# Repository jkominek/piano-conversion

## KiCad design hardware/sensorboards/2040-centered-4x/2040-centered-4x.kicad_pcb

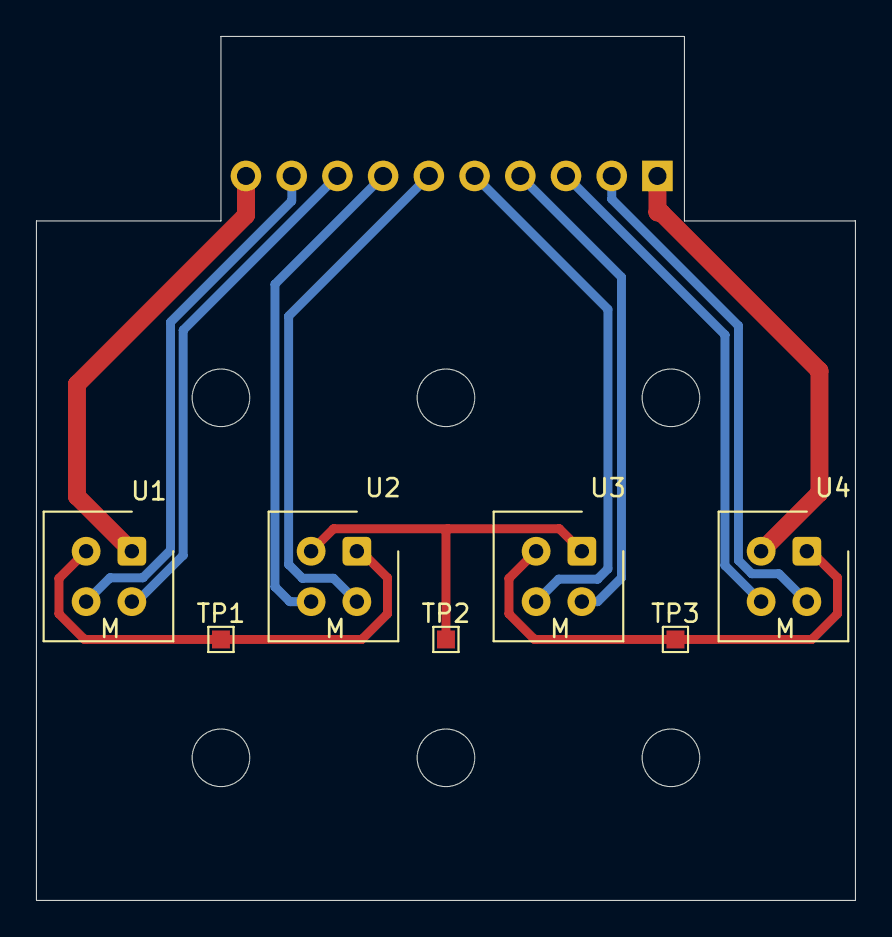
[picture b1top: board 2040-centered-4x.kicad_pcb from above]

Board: 2 copper layers, 45.5 x 48.0 mm, 14 parts (1 on the bottom side), 13 nets.

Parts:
H1, H2, H3, H4, H5, H6: MountingHole; MountingHole_3.2mm_M3
J1: Conn_01x10_Male; Pin_Header_Angled_1x10_Pitch2.54mm
TP1, TP2, TP3: TestPoint; TestPoint_Pad_1.0x1.0mm
U1, U2, U3, U4: CNY70; Vishay_CNY70

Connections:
/C1: J1.9, U1.3
/C2: J1.7, U2.3
/C3: J1.5, U3.3
/C4: J1.3, U4.3
/E1: J1.8, U1.4
/E2: J1.6, U2.4
/E3: J1.4, U3.4
/E4: J1.2, U4.4
/NEG: J1.1, U4.2
/POS: J1.10, U1.1
unnamed: TP1.1, U1.2, U2.1
unnamed: TP2.1, U2.2, U3.1
unnamed: TP3.1, U3.2, U4.1

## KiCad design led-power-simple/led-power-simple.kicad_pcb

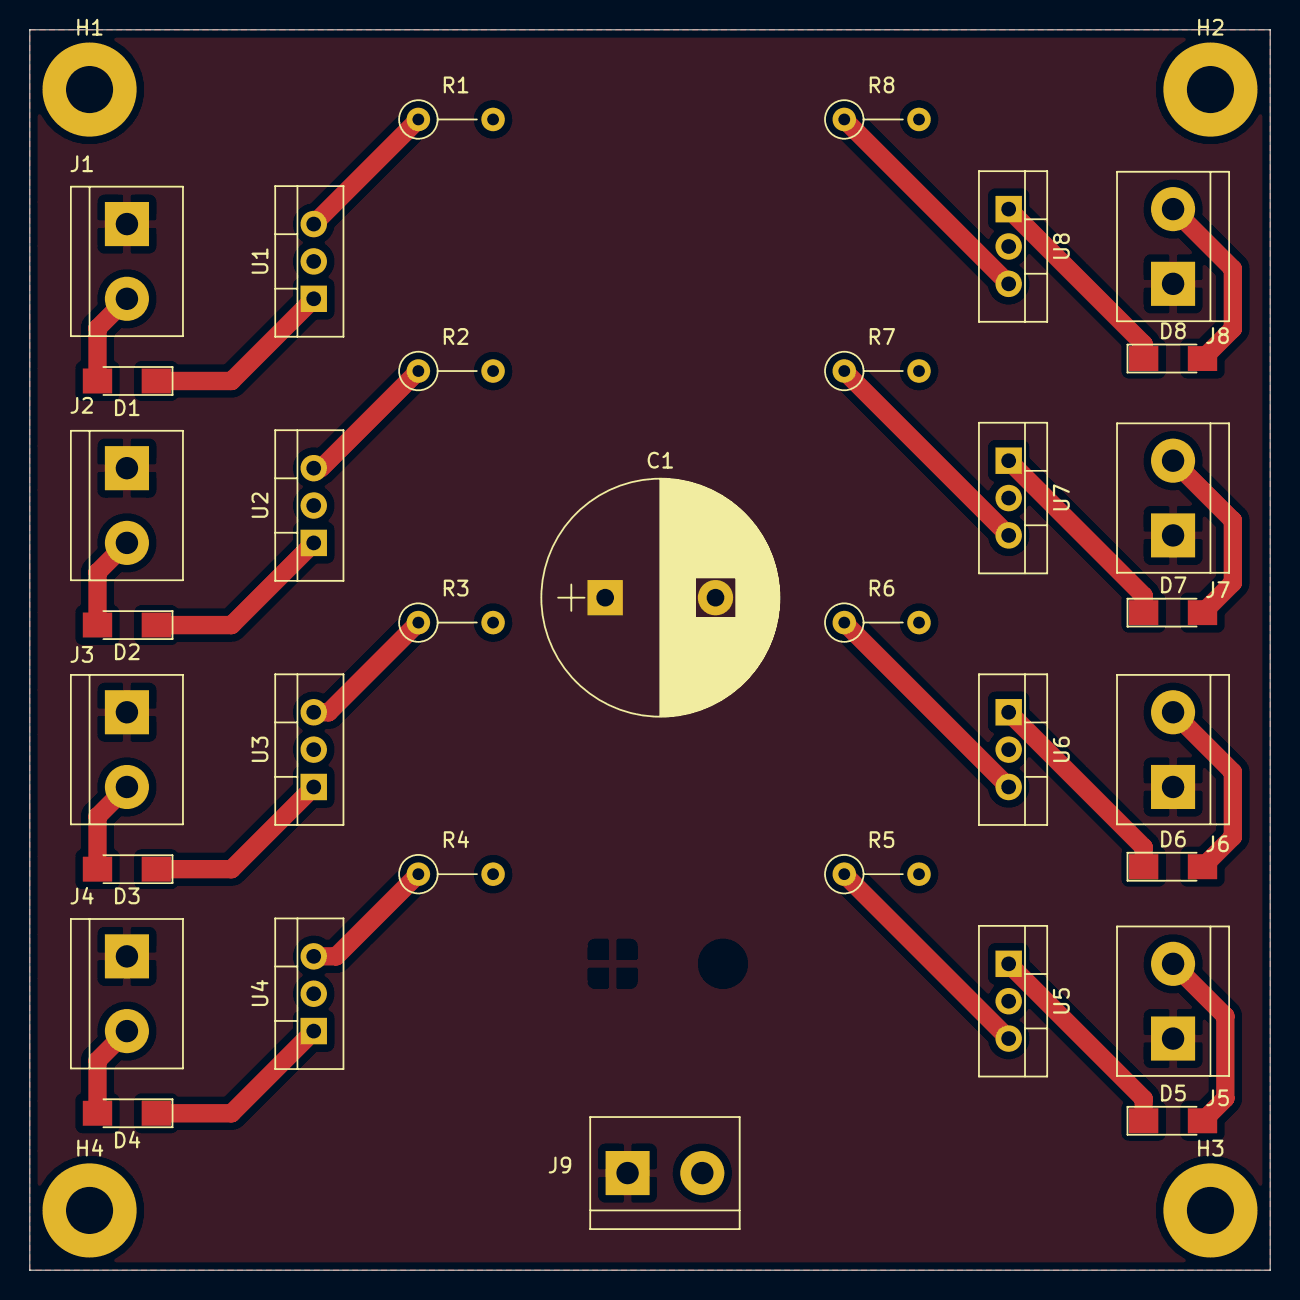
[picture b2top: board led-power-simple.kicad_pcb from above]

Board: 2 copper layers, 84.3 x 84.3 mm, 38 parts (0 on the bottom side), 26 nets.

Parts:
C1: Lots; CP_Radial_D16.0mm_P7.50mm
D1, D2, D3, D4, D5, D6, D7, D8: LED_Small; LED_1206_HandSoldering
H1, H2, H3, H4: MountingHole_Pad; MountingHole_3.2mm_M3_Pad
J1, J2, J3, J4, J5, J6, J7, J8, J9: Screw_Terminal_01x02; TerminalBlock_bornier-2_P5.08mm
R1, R2, R3, R4, R5, R6, R7, R8: 250; R_Axial_DIN0207_L6.3mm_D2.5mm_P5.08mm_Vertical
U1, U2, U3, U4, U5, U6, U7, U8: LM7809_TO220; TO-220-3_Vertical

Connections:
+48V: C1.1, J1.1, J2.1, J3.1, J4.1, J5.1, J6.1, J7.1, J8.1, J9.1
/String1: D1.2, J1.2
/String2: D2.2, J2.2
/String3: D3.2, J3.2
/String4: D4.2, J4.2
/String5: D5.2, J5.2
/String6: D6.2, J6.2
/String7: D7.2, J7.2
/String8: D8.2, J8.2
GND: C1.2, J9.2, R1.2, R2.2, R3.2, R4.2, R5.2, R6.2, R7.2, R8.2, U1.2, U2.2, U3.2, U4.2, U5.2, U6.2, U7.2, U8.2
unnamed: D1.1, U1.1
unnamed: D2.1, U2.1
unnamed: D3.1, U3.1
unnamed: D4.1, U4.1
unnamed: D5.1, U5.1
unnamed: D6.1, U6.1
unnamed: D7.1, U7.1
unnamed: D8.1, U8.1
unnamed: R1.1, U1.3
unnamed: R2.1, U2.3
unnamed: R3.1, U3.3
unnamed: R4.1, U4.3
unnamed: R5.1, U5.3
unnamed: R6.1, U6.3
unnamed: R7.1, U7.3
unnamed: R8.1, U8.3

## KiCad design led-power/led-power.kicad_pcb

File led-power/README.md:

# LED Power board

As covered in the main design doc, the board takes +15V and +48V,
and uses them to feed 8 strings of LEDs with a constant current of
~20mA.

# FAQs

* Why do we require a +15V supply?
  * A low power DIN rail +15V supply is <$10. An on-board regulator
    that could regulate the +48V down to +15V, without getting too hot,
    would cost about the same amount. There are cheaper regulators that
    could produce +5V, but we need to provide the op amps with something
    higher.
* The +15V supply is really kind of dumb, we're only drawing about 100mA.
  * Yes, and the op amps can run off of 45V. I'm considering a new
    version which runs off a single ~40V supply. But 40V supplies don't
    fall off of trees. So it isn't an obvious win.

# Design

## Constant current regulation

We've got a chain of ~22+1 LEDs, which will have a combined forward voltage
of between 30V and 37V, depending on part variation and current conditions.
We'd like to apply a constant 20mA to them. We've got a ~48V supply to work
with. The suggested supply is actually a 43V to 52V device. So we need to
be able to drop anywhere between 23V and 6V, while controlling the current.

To do this, we stack an N-channel MOSFET on top of a temperature
stable precision resistor.  The precision resistor is chosen so that
when we hold a certain fixed voltage across the resistor, 20mA is
developed through it. To hold that voltage, an op amp drives the MOSFET's
gate to whatever voltage is necessary for the MOSFET's resistance to
drop the excess voltage.

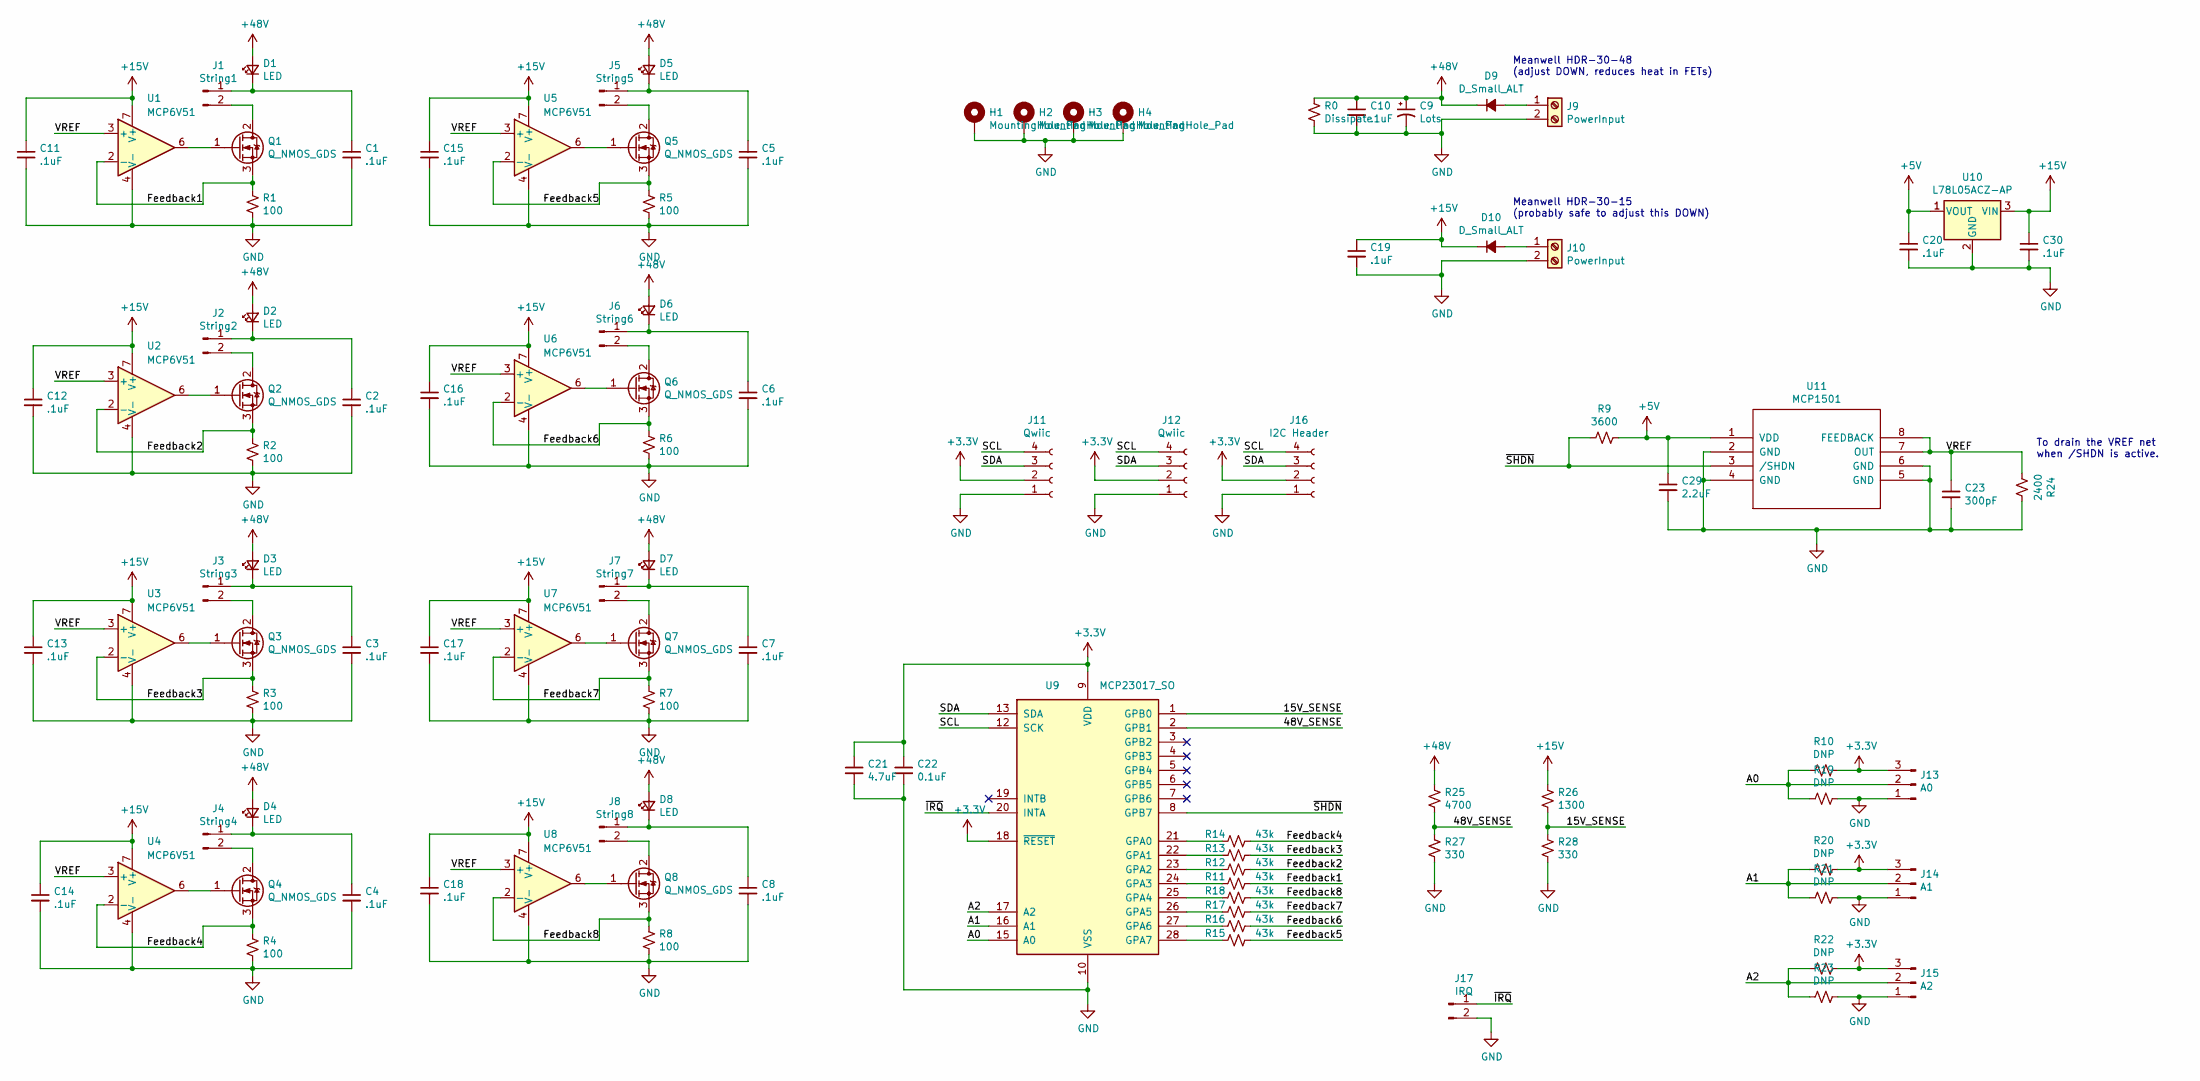
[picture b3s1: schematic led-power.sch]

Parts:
C1, C2, C3, C4, C5, C6, C7, C8, C10, C11, C12, C13, C14, C15, C16, C17, C18, C19, C20, C30: .1uF; C_0805_HandSoldering
C9: Lots; CP_Radial_D16.0mm_P7.50mm
C21: 4.7uF; C_0805_HandSoldering
C22: 0.1uF; C_0805_HandSoldering
C23: 300pF; C_0805_HandSoldering
C29: 2.2uF; C_0805_HandSoldering
D1, D2, D3, D4, D5, D6, D7, D8: LED; LED_0805_HandSoldering
D9, D10: D_Small_ALT; D_SOD-123F
H1, H2, H3, H4: MountingHole_Pad; MountingHole_3.2mm_M3_Pad_Via
J1: String1; Pin_Header_Angled_1x02_Pitch2.54mm
J2: String2; Pin_Header_Angled_1x02_Pitch2.54mm
J3: String3; Pin_Header_Angled_1x02_Pitch2.54mm
J4: String4; Pin_Header_Angled_1x02_Pitch2.54mm
J5: String5; Pin_Header_Angled_1x02_Pitch2.54mm
J6: String6; Pin_Header_Angled_1x02_Pitch2.54mm
J7: String7; Pin_Header_Angled_1x02_Pitch2.54mm
J8: String8; Pin_Header_Angled_1x02_Pitch2.54mm
J9, J10: PowerInput; TerminalBlock_bornier-2_P5.08mm
J11, J12: Qwiic; JST_SH_SM04B-SRSS-TB_04x1.00mm_Angled
J13: A0; Pin_Header_Straight_1x03_Pitch2.54mm
J14: A1; Pin_Header_Straight_1x03_Pitch2.54mm
J15: A2; Pin_Header_Straight_1x03_Pitch2.54mm
J16: I2C Header; Pin_Header_Straight_1x04_Pitch2.54mm
J17: IRQ; Pin_Header_Straight_1x02_Pitch2.54mm
Q1, Q2, Q3, Q4, Q5, Q6, Q7, Q8: Q_NMOS_GDS; TO-220-3_Vertical
R0: Dissipate; R_0805_HandSoldering
R1, R2, R3, R4, R5, R6, R7, R8: 100; R_Axial_DIN0207_L6.3mm_D2.5mm_P2.54mm_Vertical
R9: 3600; R_0805_HandSoldering
R10, R19, R20, R21, R22, R23: DNP; R_0805_HandSoldering
R11, R12, R13, R14, R15, R16, R17, R18: 43k; R_0805_HandSoldering
R24: 2400; R_0805_HandSoldering
R25: 4700; R_0805_HandSoldering
R26: 1300; R_0805_HandSoldering
R27, R28: 330; R_0805_HandSoldering
U1, U2, U3, U4, U5, U6, U7, U8: MCP6V51; MSOP-8_3x3mm_Pitch0.65mm
U9: MCP23017_SO; SOIC-28W_7.5x17.9mm_Pitch1.27mm
U10: L78L05ACZ-AP; TO-92_Inline_Wide
U11: MCP1501; SOIC-8-N

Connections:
+3V3: C21.1, C22.1, J11.2, J12.2, J13.3, J14.3, J15.3, J16.2, R10.1, R20.1, R22.1, U9.9 (VDD), U9.18 (~RESET~)
+5V: C20.1, C29.1, R9.1, U10.1 (VOUT), U11.1 (VDD)
+15V: C11.1, C12.1, C13.1, C14.1, C15.1, C16.1, C17.1, C18.1, C19.1, C30.1, D10.1 (K), R26.1, U1.7 (V+), U2.7 (V+), U3.7 (V+), U4.7 (V+), U5.7 (V+), U6.7 (V+), U7.7 (V+), U8.7 (V+), U10.3 (VIN)
+48V: C9.1, C10.1, D1.2 (A), D2.2 (A), D3.2 (A), D4.2 (A), D5.2 (A), D6.2 (A), D7.2 (A), D8.2 (A), D9.1 (K), R0.1, R25.1
/15V_SENSE: R26.2, R28.1, U9.1 (GPB0)
/48V_SENSE: R25.2, R27.1, U9.2 (GPB1)
/A0: J13.2, R10.2, R19.2, U9.15 (A0)
/A1: J14.2, R20.2, R21.2, U9.16 (A1)
/A2: J15.2, R22.2, R23.2, U9.17 (A2)
/Feedback1: Q1.3 (S), R1.1, R11.1, U1.2 (-)
/Feedback2: Q2.3 (S), R2.1, R12.1, U2.2 (-)
/Feedback3: Q3.3 (S), R3.1, R13.1, U3.2 (-)
/Feedback4: Q4.3 (S), R4.1, R14.1, U4.2 (-)
/Feedback5: Q5.3 (S), R5.1, R15.1, U5.2 (-)
/Feedback6: Q6.3 (S), R6.1, R16.1, U6.2 (-)
/Feedback7: Q7.3 (S), R7.1, R17.1, U7.2 (-)
/Feedback8: Q8.3 (S), R8.1, R18.1, U8.2 (-)
/SCL: J11.4, J12.4, J16.4, U9.12 (SCK)
/SDA: J11.3, J12.3, J16.3, U9.13 (SDA)
/VREF: C23.1, R24.2, U1.3 (+), U2.3 (+), U3.3 (+), U4.3 (+), U5.3 (+), U6.3 (+), U7.3 (+), U8.3 (+), U11.7 (OUT), U11.8 (FEEDBACK)
/~IRQ: J17.1, U9.20 (INTA)
/~SHDN: R9.2, U9.8 (GPB7), U11.3 (/SHDN)
GND: C1.2, C2.2, C3.2, C4.2, C5.2, C6.2, C7.2, C8.2, C9.2, C10.2, C11.2, C12.2, C13.2, C14.2, C15.2, C16.2, C17.2, C18.2, C19.2, C20.2, C21.2, C22.2, C23.2, C29.2, C30.2, H1.1, H2.1, H3.1, H4.1, J9.2, J10.2, J11.1, J12.1, J13.1, J14.1, J15.1, J16.1, J17.2, R0.2, R1.2, R2.2, R3.2, R4.2, R5.2, R6.2, R7.2, R8.2, R19.1, R21.1, R23.1, R24.1, R27.2, R28.2, U1.4 (V-), U2.4 (V-), U3.4 (V-), U4.4 (V-), U5.4 (V-), U6.4 (V-), U7.4 (V-), U8.4 (V-), U9.10 (VSS), U10.2 (GND), U11.2 (GND), U11.4 (GND), U11.5 (GND), U11.6 (GND)
unnamed: C1.1, D1.1 (K), J1.1
unnamed: C2.1, D2.1 (K), J2.1
unnamed: C3.1, D3.1 (K), J3.1
unnamed: C4.1, D4.1 (K), J4.1
unnamed: C5.1, D5.1 (K), J5.1
unnamed: C6.1, D6.1 (K), J6.1
unnamed: C7.1, D7.1 (K), J7.1
unnamed: C8.1, D8.1 (K), J8.1
unnamed: D9.2 (A), J9.1
unnamed: D10.2 (A), J10.1
unnamed: J1.2, Q1.2 (D)
unnamed: J2.2, Q2.2 (D)
unnamed: J3.2, Q3.2 (D)
unnamed: J4.2, Q4.2 (D)
unnamed: J5.2, Q5.2 (D)
unnamed: J6.2, Q6.2 (D)
unnamed: J7.2, Q7.2 (D)
unnamed: J8.2, Q8.2 (D)
unnamed: Q1.1 (G), U1.6
unnamed: Q2.1 (G), U2.6
unnamed: Q3.1 (G), U3.6
unnamed: Q4.1 (G), U4.6
unnamed: Q5.1 (G), U5.6
unnamed: Q6.1 (G), U6.6
unnamed: Q7.1 (G), U7.6
unnamed: Q8.1 (G), U8.6
unnamed: R11.2, U9.24 (GPA3)
unnamed: R12.2, U9.23 (GPA2)
unnamed: R13.2, U9.22 (GPA1)
unnamed: R14.2, U9.21 (GPA0)
unnamed: R15.2, U9.28 (GPA7)
unnamed: R16.2, U9.27 (GPA6)
unnamed: R17.2, U9.26 (GPA5)
unnamed: R18.2, U9.25 (GPA4)

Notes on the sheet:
Meanwell HDR-30-48 (adjust DOWN, reduces heat in FETs)
Meanwell HDR-30-15 (probably safe to adjust this DOWN)
To drain the VREF net when /SHDN is active.

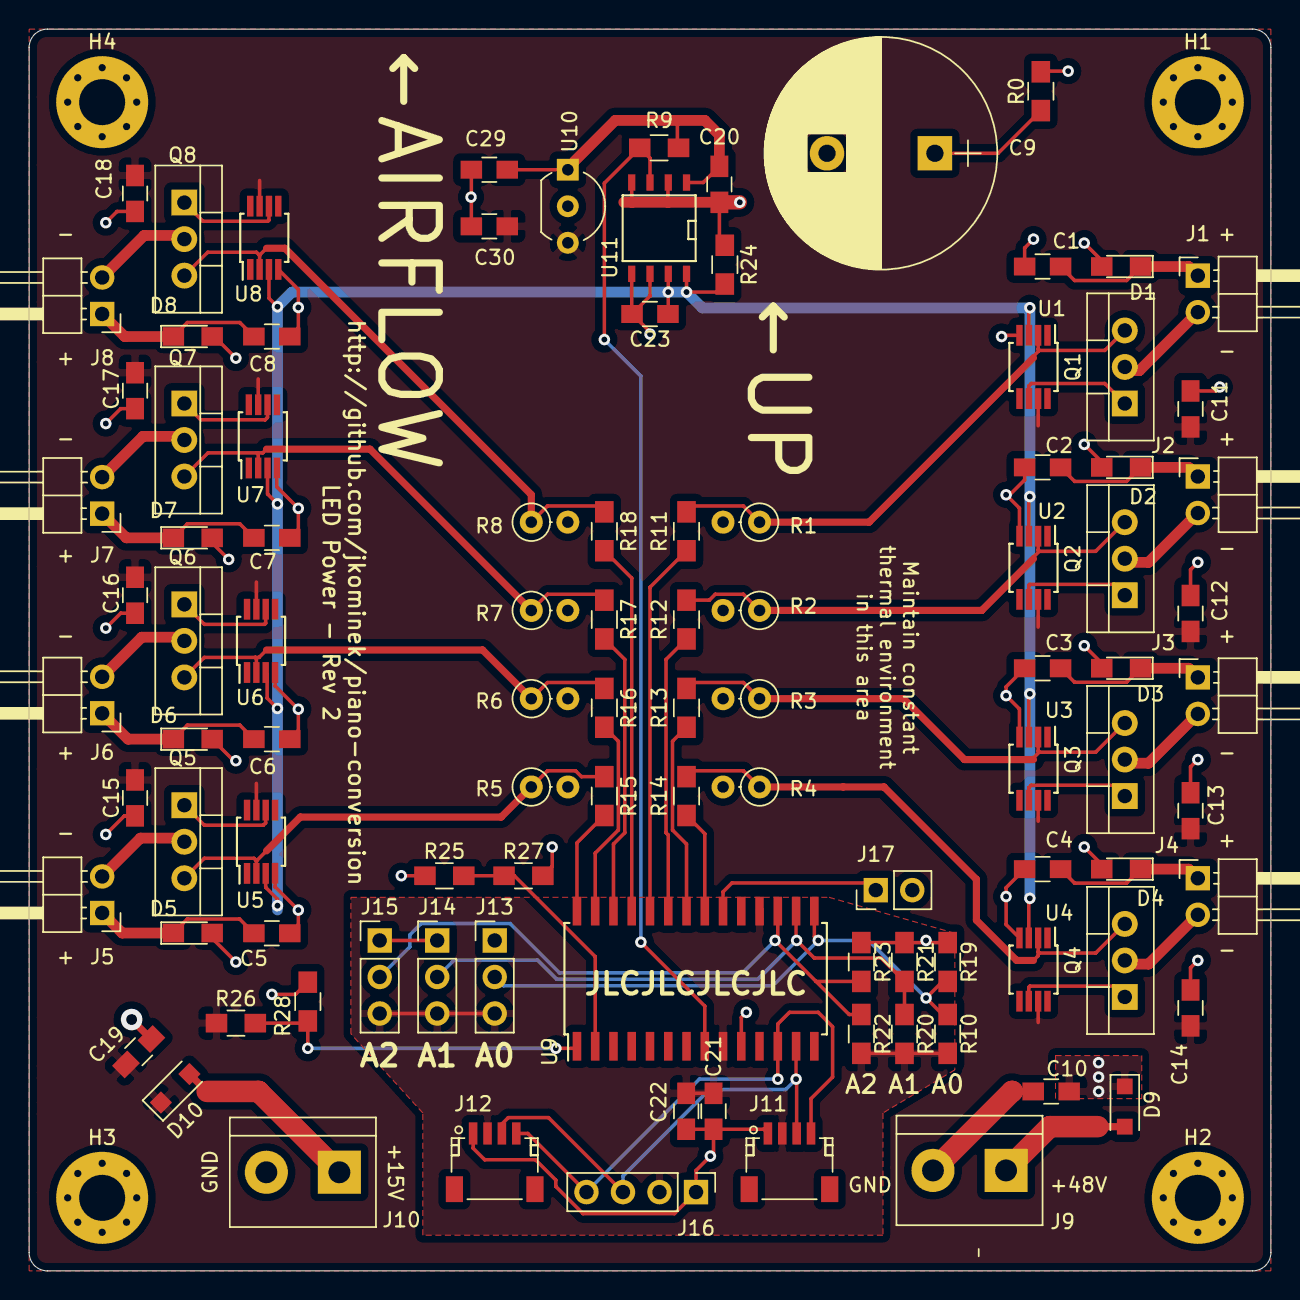
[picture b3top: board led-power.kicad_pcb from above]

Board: 4 copper layers, 86.4 x 86.4 mm, 104 parts (0 on the bottom side), 57 nets.

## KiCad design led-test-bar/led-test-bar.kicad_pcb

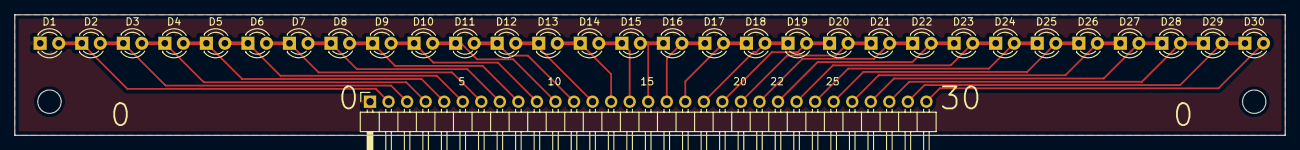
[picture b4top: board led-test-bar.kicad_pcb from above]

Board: 2 copper layers, 174.0 x 16.5 mm, 33 parts (0 on the bottom side), 31 nets.

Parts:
D1, D2, D3, D4, D5, D6, D7, D8, D9, D10, D11, D12, D13, D14, D15, D16, D17, D18, D19, D20, D21, D22, D23, D24, D25, D26, D27, D28, D29, D30: LED_Small; LED_D3.0mm
H1, H2: MountingHole; MountingHole_3.2mm_M3
J1: Conn_01x31_Male; Pin_Header_Angled_1x31_Pitch2.54mm

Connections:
unnamed: D1.1, J1.1
unnamed: D1.2, D2.1, J1.2
unnamed: D2.2, D3.1, J1.3
unnamed: D3.2, D4.1, J1.4
unnamed: D4.2, D5.1, J1.5
unnamed: D5.2, D6.1, J1.6
unnamed: D6.2, D7.1, J1.7
unnamed: D7.2, D8.1, J1.8
unnamed: D8.2, D9.1, J1.9
unnamed: D9.2, D10.1, J1.10
unnamed: D10.2, D11.1, J1.11
unnamed: D11.2, D12.1, J1.12
unnamed: D12.2, D13.1, J1.13
unnamed: D13.2, D14.1, J1.14
unnamed: D14.2, D15.1, J1.15
unnamed: D15.2, D16.1, J1.16
unnamed: D16.2, D17.1, J1.17
unnamed: D17.2, D18.1, J1.18
unnamed: D18.2, D19.1, J1.19
unnamed: D19.2, D20.1, J1.20
unnamed: D20.2, D21.1, J1.21
unnamed: D21.2, D22.1, J1.22
unnamed: D22.2, D23.1, J1.23
unnamed: D23.2, D24.1, J1.24
unnamed: D24.2, D25.1, J1.25
unnamed: D25.2, D26.1, J1.26
unnamed: D26.2, D27.1, J1.27
unnamed: D27.2, D28.1, J1.28
unnamed: D28.2, D29.1, J1.29
unnamed: D29.2, D30.1, J1.30
unnamed: D30.2, J1.31

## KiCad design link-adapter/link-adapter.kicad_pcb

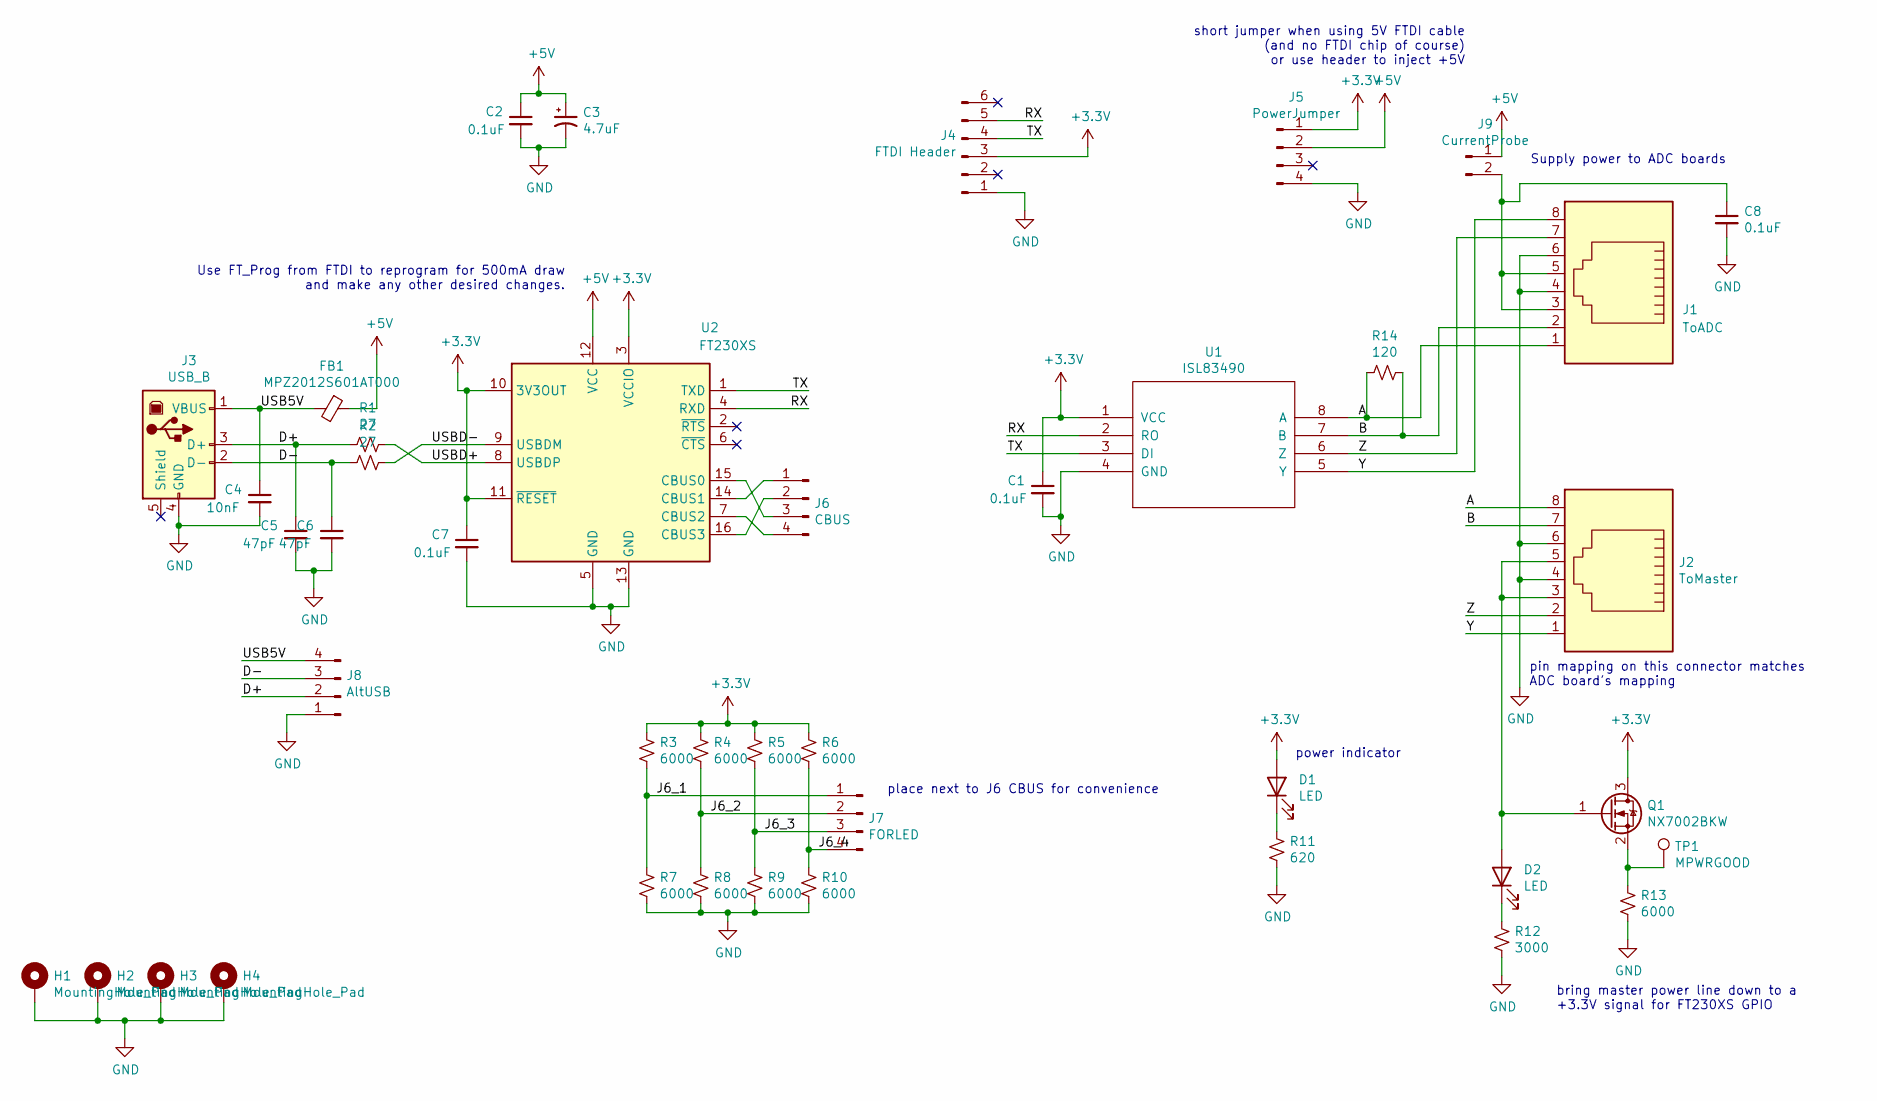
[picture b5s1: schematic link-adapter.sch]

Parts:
C1, C2, C7, C8: 0.1uF; C_0805_HandSoldering
C3: 4.7uF; C_0805_HandSoldering
C4: 10nF; C_0805_HandSoldering
C5, C6: 47pF; C_0805_HandSoldering
D1, D2: LED; LED_0805_HandSoldering
FB1: MPZ2012S601AT000‎; L_0805_HandSoldering
H1, H2, H3, H4: MountingHole_Pad; MountingHole_3.2mm_M3_Pad
J1: ToADC; RJ45_8
J2: ToMaster; RJ45_8
J3: USB_B
J4: FTDI Header; Pin_Header_Straight_1x06_Pitch2.54mm
J5: PowerJumper; Pin_Header_Straight_1x04_Pitch2.54mm
J6: CBUS; Pin_Header_Straight_1x04_Pitch2.54mm
J7: FORLED; Pin_Header_Straight_1x04_Pitch2.54mm
J8: AltUSB; Pin_Header_Straight_1x04_Pitch2.54mm
J9: CurrentProbe; Pin_Header_Straight_1x02_Pitch2.54mm
Q1: NX7002BKW; SOT-323_SC-70_Handsoldering
R1, R2: 27; R_0805_HandSoldering
R3, R4, R5, R6, R7, R8, R9, R10, R13: 6000; R_0805_HandSoldering
R11: 620; R_0805_HandSoldering
R12: 3000; R_0805_HandSoldering
R14: 120; R_0805_HandSoldering
TP1: MPWRGOOD; Pin_Header_Straight_1x01_Pitch2.54mm
U1: ISL83490; SOIC-8-N
U2: FT230XS; SSOP-16_3.9x4.9mm_Pitch0.635mm

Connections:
+3V3: C1.1, C7.1, D1.2 (A), J4.3, J5.1, Q1.3 (D), R3.1, R4.1, R5.1, R6.1, U1.1 (VCC), U2.3 (VCCIO), U2.10 (3V3OUT), U2.11 (~RESET)
+5V: C2.1, C3.1, FB1.1, J5.2, J9.1, U2.12 (VCC)
/A: J1.1, J2.8, R14.2, U1.8 (A)
/B: J1.2, J2.7, R14.1, U1.7 (B)
/CBUS0: J6.3, U2.15 (CBUS0)
/CBUS1: J6.1, U2.14 (CBUS1)
/CBUS2: J6.4, U2.7 (CBUS2)
/CBUS3: J6.2, U2.16 (CBUS3)
/D+: C5.1, J3.3 (D+), J8.2, R1.2
/D-: C6.1, J3.2 (D-), J8.3, R2.2
/J6_1: J7.1, R3.2, R7.1
/J6_2: J7.2, R4.2, R8.1
/J6_3: J7.3, R5.2, R9.1
/J6_4: J7.4, R6.2, R10.1
/RX: J4.5, U1.2 (RO), U2.4 (RXD)
/TX: J4.4, U1.3 (DI), U2.1 (TXD)
/USB5V: C4.1, FB1.2, J3.1 (VBUS), J8.4
/USBD+: R1.1, U2.8 (USBDP)
/USBD-: R2.1, U2.9 (USBDM)
/Y: J1.8, J2.1, U1.5 (Y)
/Z: J1.7, J2.2, U1.6 (Z)
GND: C1.2, C2.2, C3.2, C4.2, C5.2, C6.2, C7.2, C8.2, H1.1, H2.1, H3.1, H4.1, J1.4, J1.6, J2.4, J2.6, J3.4 (GND), J4.1, J5.4, J8.1, R7.2, R8.2, R9.2, R10.2, R11.2, R12.2, R13.2, U1.4 (GND), U2.5 (GND), U2.13 (GND)
unnamed: C8.1, J1.3, J1.5, J9.2
unnamed: D1.1 (K), R11.1
unnamed: D2.1 (K), R12.1
unnamed: D2.2 (A), J2.3, J2.5, Q1.1 (G)
unnamed: Q1.2 (S), R13.1, TP1.1

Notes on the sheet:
Supply power to ADC boards
place next to J6 CBUS for convenience
short jumper when using 5V FTDI cable (and no FTDI chip of course) or use header to inject +5V
Use FT_Prog from FTDI to reprogram for 500mA draw and make any other desired changes.
power indicator
bring master power line down to a +3.3V signal for FT230XS GPIO
pin mapping on this connector matches ADC board's mapping

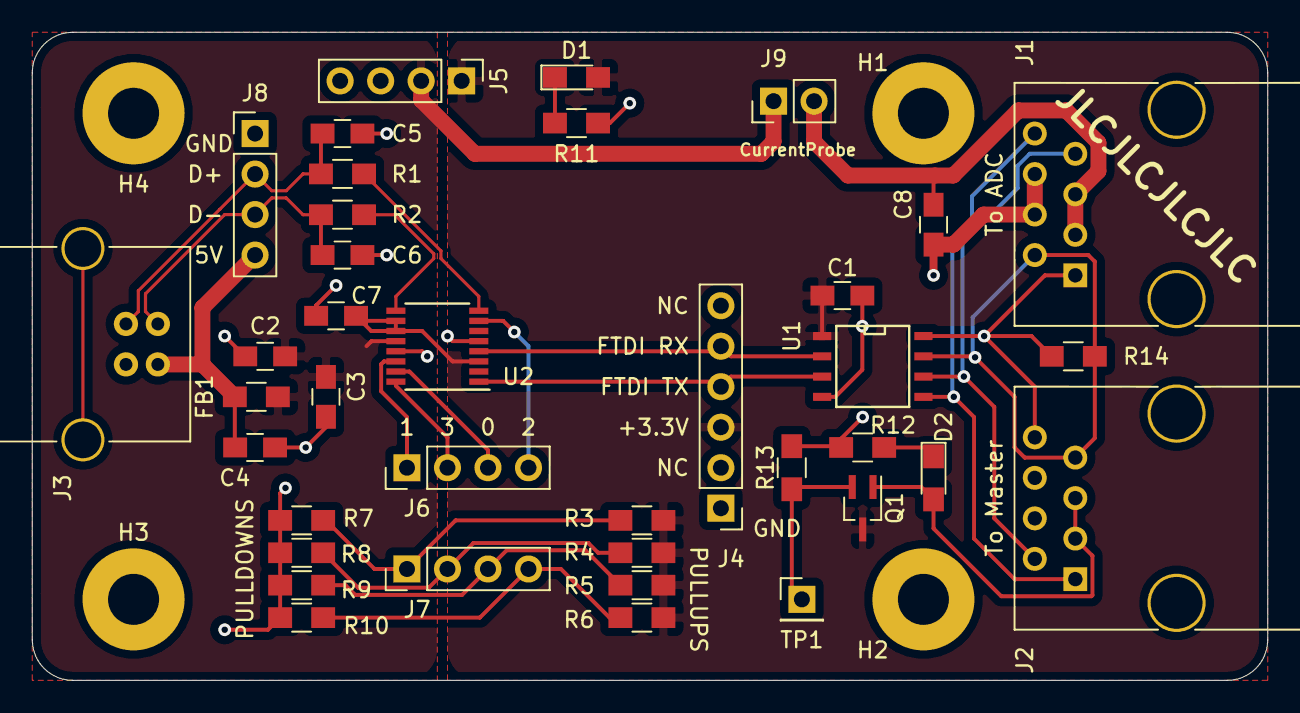
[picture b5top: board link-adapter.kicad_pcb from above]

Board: 2 copper layers, 77.5 x 40.6 mm, 42 parts (0 on the bottom side), 27 nets.
